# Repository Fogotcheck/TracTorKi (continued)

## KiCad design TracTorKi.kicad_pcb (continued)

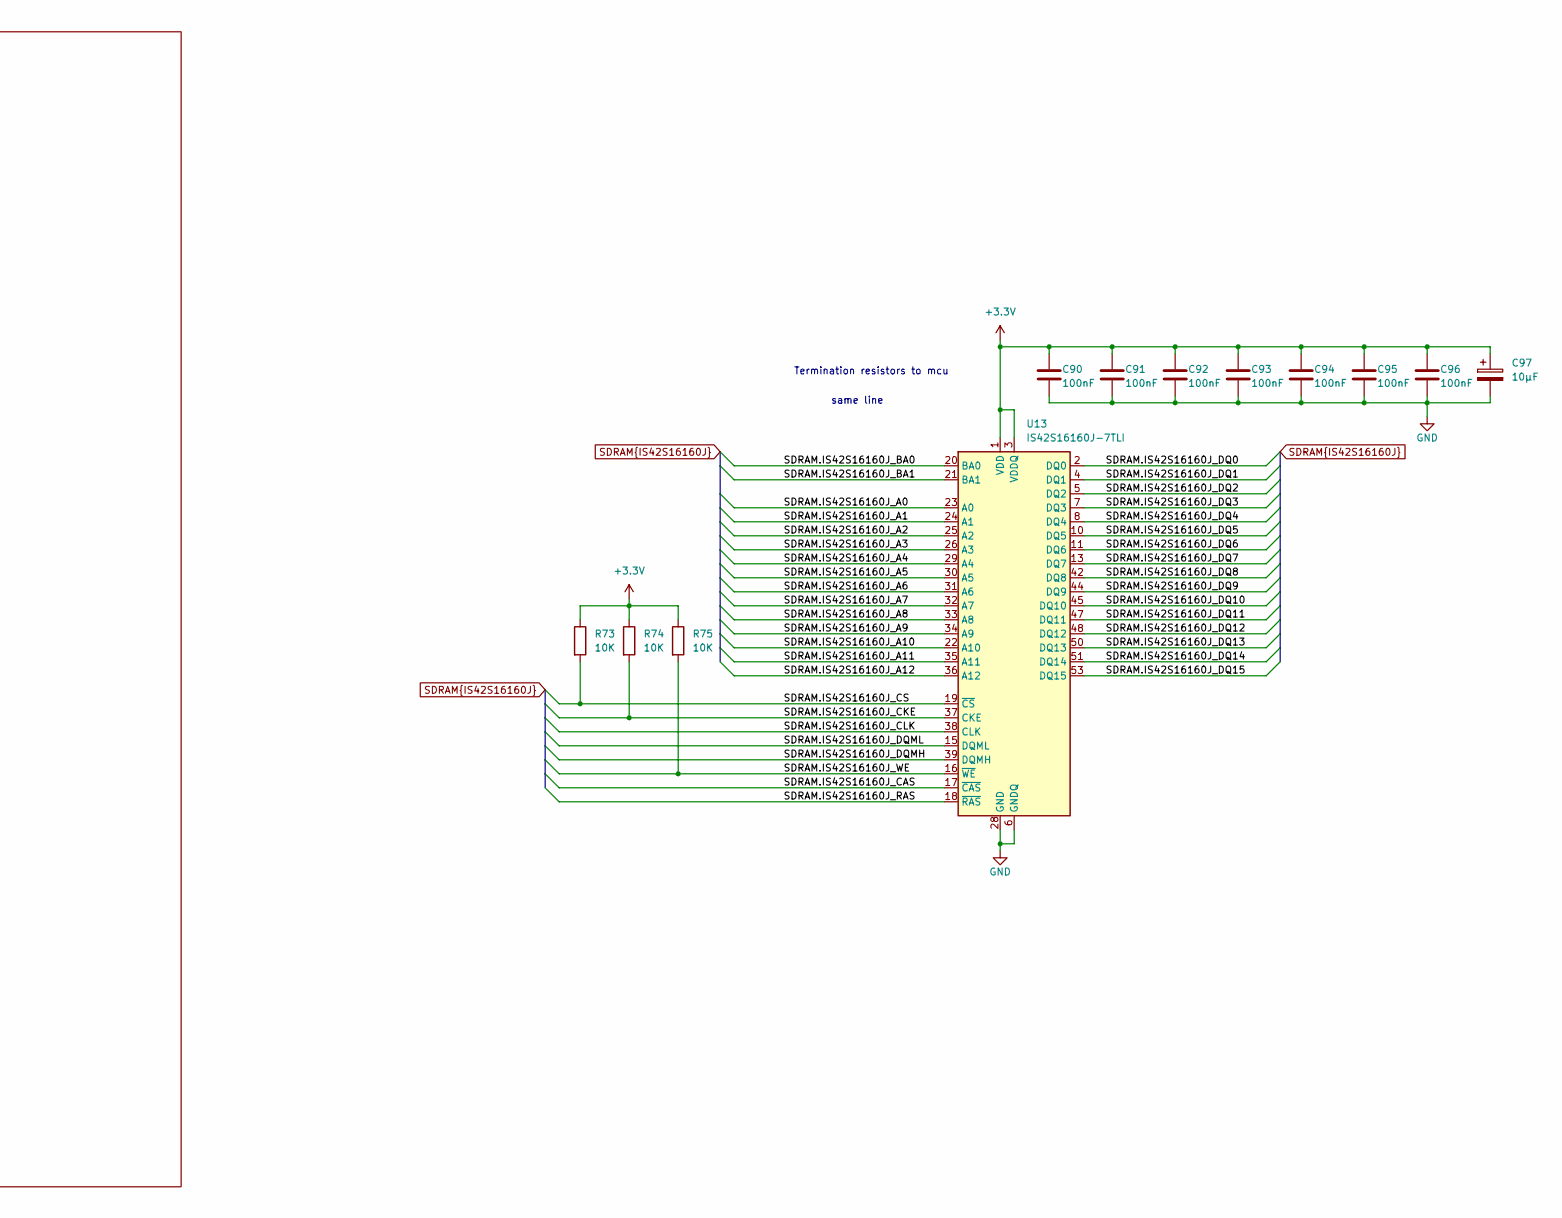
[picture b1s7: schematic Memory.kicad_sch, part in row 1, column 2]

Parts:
C90, C91, C92, C93, C94, C95, C96: 100nF; C_0402_1005Metric_Pad0.74x0.62mm_HandSolder
C97: 10µF; CP_EIA-3216-18_Kemet-A_HandSolder
R73, R74, R75: 10K; R_0603_1608Metric_Pad0.98x0.95mm_HandSolder
U13: IS42S16160J-7TLI; TSOP-II-54_22.2x10.16mm_P0.8mm

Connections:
+3.3V: C90.1, C91.1, C92.1, C93.1, C94.1, C95.1, C96.1, C97.1, R73.1, R74.1, R75.1, U13.1 (VDD), U13.3 (VDDQ), U13.9 (VDDQ), U13.14 (VDD), U13.27 (VDD), U13.43 (VDDQ), U13.49 (VDDQ); also elsewhere on the board
GND: C90.2, C91.2, C92.2, C93.2, C94.2, C95.2, C96.2, C97.2, U13.6 (GNDQ), U13.12 (GNDQ), U13.28 (GND), U13.41 (GND), U13.46 (GNDQ), U13.52 (GNDQ), U13.54 (GND); also elsewhere on the board
SDRAM.IS42S16160J_A0: U13.23 (A0); also elsewhere on the board
SDRAM.IS42S16160J_A1: U13.24 (A1); also elsewhere on the board
SDRAM.IS42S16160J_A2: U13.25 (A2); also elsewhere on the board
SDRAM.IS42S16160J_A3: U13.26 (A3); also elsewhere on the board
SDRAM.IS42S16160J_A4: U13.29 (A4); also elsewhere on the board
SDRAM.IS42S16160J_A5: U13.30 (A5); also elsewhere on the board
SDRAM.IS42S16160J_A6: U13.31 (A6); also elsewhere on the board
SDRAM.IS42S16160J_A7: U13.32 (A7); also elsewhere on the board
SDRAM.IS42S16160J_A8: U13.33 (A8); also elsewhere on the board
SDRAM.IS42S16160J_A9: U13.34 (A9); also elsewhere on the board
SDRAM.IS42S16160J_A10: U13.22 (A10); also elsewhere on the board
SDRAM.IS42S16160J_A11: U13.35 (A11); also elsewhere on the board
SDRAM.IS42S16160J_A12: U13.36 (A12); also elsewhere on the board
SDRAM.IS42S16160J_BA0: U13.20 (BA0); also elsewhere on the board
SDRAM.IS42S16160J_BA1: U13.21 (BA1); also elsewhere on the board
SDRAM.IS42S16160J_CAS: U13.17 (~CAS); also elsewhere on the board
SDRAM.IS42S16160J_CKE: R74.2, U13.37 (CKE); also elsewhere on the board
SDRAM.IS42S16160J_CLK: U13.38 (CLK); also elsewhere on the board
SDRAM.IS42S16160J_CS: R73.2, U13.19 (~CS); also elsewhere on the board
SDRAM.IS42S16160J_DQ0: U13.2 (DQ0); also elsewhere on the board
SDRAM.IS42S16160J_DQ1: U13.4 (DQ1); also elsewhere on the board
SDRAM.IS42S16160J_DQ2: U13.5 (DQ2); also elsewhere on the board
SDRAM.IS42S16160J_DQ3: U13.7 (DQ3); also elsewhere on the board
SDRAM.IS42S16160J_DQ4: U13.8 (DQ4); also elsewhere on the board
SDRAM.IS42S16160J_DQ5: U13.10 (DQ5); also elsewhere on the board
SDRAM.IS42S16160J_DQ6: U13.11 (DQ6); also elsewhere on the board
SDRAM.IS42S16160J_DQ7: U13.13 (DQ7); also elsewhere on the board
SDRAM.IS42S16160J_DQ8: U13.42 (DQ8); also elsewhere on the board
SDRAM.IS42S16160J_DQ9: U13.44 (DQ9); also elsewhere on the board
SDRAM.IS42S16160J_DQ10: U13.45 (DQ10); also elsewhere on the board
SDRAM.IS42S16160J_DQ11: U13.47 (DQ11); also elsewhere on the board
SDRAM.IS42S16160J_DQ12: U13.48 (DQ12); also elsewhere on the board
SDRAM.IS42S16160J_DQ13: U13.50 (DQ13); also elsewhere on the board
SDRAM.IS42S16160J_DQ14: U13.51 (DQ14); also elsewhere on the board
SDRAM.IS42S16160J_DQ15: U13.53 (DQ15); also elsewhere on the board
SDRAM.IS42S16160J_DQMH: U13.39 (DQMH); also elsewhere on the board
SDRAM.IS42S16160J_DQML: U13.15 (DQML); also elsewhere on the board
SDRAM.IS42S16160J_RAS: U13.18 (~RAS); also elsewhere on the board
SDRAM.IS42S16160J_WE: R75.2, U13.16 (~WE); also elsewhere on the board

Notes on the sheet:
Termination resistors to mcu
same line

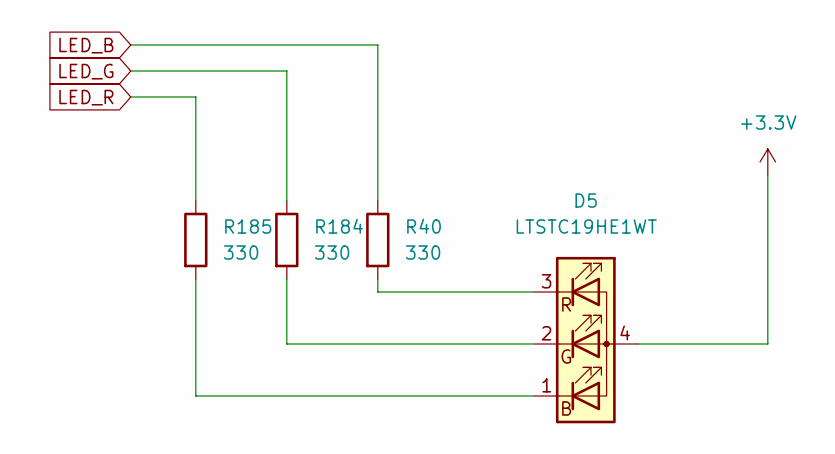
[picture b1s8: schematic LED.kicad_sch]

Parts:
D5: LTSTC19HE1WT; LED_LiteOn_LTST-C19HE1WT
R40, R184, R185: 330; R_0603_1608Metric_Pad0.98x0.95mm_HandSolder

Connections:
+3.3V: D5.4 (A); also elsewhere on the board
LED_B: R40.1; also elsewhere on the board
LED_G: R184.1; also elsewhere on the board
LED_R: R185.1; also elsewhere on the board
unnamed: D5.1 (BK), R185.2
unnamed: D5.2 (GK), R184.2
unnamed: D5.3 (RK), R40.2

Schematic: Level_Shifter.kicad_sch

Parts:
C135, C136: 0.1µF; C_0603_1608Metric_Pad1.08x0.95mm_HandSolder
R38, R41: 20K; R_0603_1608Metric_Pad0.98x0.95mm_HandSolder
R175, R176, R177, R178, R179, R180, R181, R182, R183: 4.7K; R_0603_1608Metric_Pad0.98x0.95mm_HandSolder
U19: TCA9517ADGK; VSSOP-8_3x3mm_P0.65mm

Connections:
+3.3V: C136.1, R175.1, R176.1, R180.1, R181.1, R182.1, R183.1, U19.1 (VCCA); also elsewhere on the board
+5V: C135.1, R177.1, R178.1, R179.1, U19.8 (VCCB); also elsewhere on the board
BQ25798_CE: R41.1; also elsewhere on the board
BQ25798_INT: R183.2; also elsewhere on the board
BQ25798_QON: R181.2; also elsewhere on the board
BQ25798_SCL: R179.2, U19.7 (SCLB); also elsewhere on the board
BQ25798_SDA: R178.2, U19.6 (SDAB); also elsewhere on the board
BQ25798_STAT: R182.2; also elsewhere on the board
GND: C135.2, C136.2, R38.2, R41.2, U19.4 (GND); also elsewhere on the board
unnamed: R177.2, U19.5 (EN)
POWER_I2C_SCL: R175.2, U19.2 (SCLA); also elsewhere on the board
POWER_I2C_SDA: R176.2, U19.3 (SDAA); also elsewhere on the board
STUSB4500_INT: R180.2; also elsewhere on the board
STUSB4500_RST: R38.1; also elsewhere on the board

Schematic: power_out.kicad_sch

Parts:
C37, C38, C44, C45, C46, C47, C52, C53, C54, C55, C63, C64, C65, C66: 22µF; C_0603_1608Metric_Pad1.08x0.95mm_HandSolder
C39, C43, C51, C62: 0.1µF; C_0603_1608Metric_Pad1.08x0.95mm_HandSolder
C40, C48, C57: 10µF; C_1206_3216Metric_Pad1.33x1.80mm_HandSolder; voltage 50V
C41, C50, C61: 1µF; C_0603_1608Metric_Pad1.08x0.95mm_HandSolder
C42, C49, C58: 220nF; C_1206_3216Metric_Pad1.33x1.80mm_HandSolder; voltage 50V
C56: 33µF; CP_EIA-7343-31_Kemet-D_HandSolder; voltage 50V
L2: 8.2µH; L_Chilisin_BMRx00060630
L3: 15µH; L_Chilisin_BMRx00060630
L4: 6.8µH; L_Chilisin_BMRx00060630
R32: 3.57; R_0603_1608Metric_Pad0.98x0.95mm_HandSolder
R33: 1.15; R_0603_1608Metric_Pad0.98x0.95mm_HandSolder
R34, R36, R39: 100K; R_0603_1608Metric_Pad0.98x0.95mm_HandSolder
R35: 24.9K; R_0603_1608Metric_Pad0.98x0.95mm_HandSolder
R37: 9.09K; R_0603_1608Metric_Pad0.98x0.95mm_HandSolder
R42: 38.3K; R_0603_1608Metric_Pad0.98x0.95mm_HandSolder
U4, U5, U6: LMR33630ADDA; Texas_HSOP-8-1EP_3.9x4.9mm_P1.27mm_ThermalVias
U7: TPS7A9201DSKR; Texas_S-PDSO-N10_EP1.2x2mm

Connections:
3.6V: C38.1, C63.1, C64.1, C65.1, C66.1, L4.2, R39.1, U7.7 (EN), U7.9 (IN), U7.10 (IN)
+3.3V: C37.1, R32.2, U7.1 (OUT), U7.2 (OUT); also elsewhere on the board
+5V: C44.1, C45.1, C46.1, C47.1, L2.2, R34.1; also elsewhere on the board
+12V: C52.1, C53.1, C54.1, C55.1, C56.1, L3.2, R36.1; also elsewhere on the board
GND: C37.2, C38.2, C39.2, C40.2, C41.2, C42.2, C44.2, C45.2, C46.2, C47.2, C48.2, C49.2, C50.2, C52.2, C53.2, C54.2, C55.2, C56.2, C57.2, C58.2, C61.2, C63.2, C64.2, C65.2, C66.2, R33.2, R35.2, R37.2, R42.2, U4.1 (GND), U4.9 (GND), U5.1 (GND), U5.9 (GND), U6.1 (GND), U6.9 (GND), U7.4 (GND), U7.6 (SS_CTRL), U7.11 (GND); also elsewhere on the board
unnamed: C43.1, C43.2, L3.1, U4.7 (BOOT), U4.8 (SW)
unnamed: R36.2, R37.1, U4.5 (FB)
unnamed: C50.1, U4.6 (VCC)
unnamed: C51.1, C51.2, L2.1, U5.7 (BOOT), U5.8 (SW)
unnamed: R34.2, R35.1, U5.5 (FB)
unnamed: C41.1, U5.6 (VCC)
unnamed: C62.1, C62.2, L4.1, U6.7 (BOOT), U6.8 (SW)
unnamed: R39.2, R42.1, U6.5 (FB)
unnamed: C61.1, U6.6 (VCC)
unnamed: R32.1, R33.1, U7.3 (FB)
unnamed: C39.1, U7.8 (NR/SS)
SYSTEM_LOAD: C40.1, C42.1, C48.1, C49.1, C57.1, C58.1, U4.2 (VIN), U4.3 (EN), U5.2 (VIN), U5.3 (EN), U6.2 (VIN), U6.3 (EN); also elsewhere on the board

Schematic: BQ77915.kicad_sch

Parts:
C30, C31: 1µF; C_1206_3216Metric_Pad1.33x1.80mm_HandSolder; voltage X7R, 50V
C32, C33, C34, C35, C36: 1µF; C_0603_1608Metric_Pad1.08x0.95mm_HandSolder
C67, C68, C69: 0.1µF; C_0603_1608Metric_Pad1.08x0.95mm_HandSolder
J2: Conn_01x03_Pin; Molex_Micro-Latch_53254-0370_1x03_P2.00mm_Horizontal
J15: Conn_01x05_Pin; Molex_Micro-Fit_3.0_43650-0500_1x05_P3.00mm_Horizontal
Q4, Q5: CSD17577Q3A; VSON-8_3.3x3.3mm_P0.65mm_NexFET
R16: 470; R_1206_3216Metric_Pad1.30x1.75mm_HandSolder
R17, R18, R19, R20, R21, R25: 1K; R_0603_1608Metric_Pad0.98x0.95mm_HandSolder
R22: 1mΩ; R_2512_6332Metric_Pad1.40x3.35mm_HandSolder
R23: 4.5K; R_0603_1608Metric_Pad0.98x0.95mm_HandSolder
R24, R26: 1M; R_0603_1608Metric_Pad0.98x0.95mm_HandSolder
R27: 470K; R_0603_1608Metric_Pad0.98x0.95mm_HandSolder
R28, R30: 10K; R_0603_1608Metric_Pad0.98x0.95mm_HandSolder
R29: 604K; R_0603_1608Metric_Pad0.98x0.95mm_HandSolder
R31: 10K; R_1206_3216Metric_Pad1.30x1.75mm_HandSolder
R43, R44: 100; R_0603_1608Metric_Pad0.98x0.95mm_HandSolder
U3: BQ7791500PWR; TSSOP-24_4.4x7.8mm_P0.65mm

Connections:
BAT_1: J15.4, R20.1
BAT_2: J15.3, R19.1
BAT_3: J15.2, R18.1
BAT_4: J15.1, R16.1, R17.1; also elsewhere on the board
BAT_GND: C35.1, C36.2, C67.1, C67.2, C69.1, J15.5, R21.1, R22.1, R28.2, R29.2, R44.2, U3.9 (VSS), U3.23 (CTRC), U3.24 (CTRD)
BQ25798_NTC: J2.2; also elsewhere on the board
BQ77915_NTC: J2.1, R30.2, U3.18 (TS)
BQ77915_SHUNT: C69.2, Q4.1 (S), Q4.2 (S), Q4.3 (S), R22.2, R24.2, R43.2
BQ77915_SRN: C68.2, R43.1, U3.11 (SRN)
BQ77915_SRP: C68.1, R44.1, U3.10 (SRP)
GND: C30.2, C31.1, J2.3, Q5.1 (S), Q5.2 (S), Q5.3 (S), R26.2, R27.2; also elsewhere on the board
unnamed: Q4.5 (D), Q5.5 (D)
unnamed: Q4.4 (G), R23.2, R24.1
unnamed: Q5.4 (G), R25.2, R26.1
unnamed: C30.1, U3.2 (AVDD), U3.20 (CCFG)
unnamed: R28.1, U3.16 (CBI)
unnamed: R25.1, U3.13 (CHG)
unnamed: R23.1, U3.12 (DSG)
unnamed: R27.1, U3.14 (LD)
unnamed: R29.1, U3.17 (OCDP)
unnamed: R31.2, U3.22 (PRES)
unnamed: C36.1, R21.2, U3.8 (VC0)
unnamed: C34.1, C35.2, R20.2, U3.7 (VC1)
unnamed: C33.1, C34.2, R19.2, U3.6 (VC2)
unnamed: C32.1, C33.2, R18.2, U3.5 (VC3)
unnamed: C32.2, R17.2, U3.3 (VC5), U3.4 (VC4)
unnamed: C31.2, R16.2, R31.1, U3.1 (VDD)
unnamed: R30.1, U3.19 (VTB)

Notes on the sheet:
дифференциальная пара

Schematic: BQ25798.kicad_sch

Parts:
C6: 4.7 µF; C_1206_3216Metric_Pad1.33x1.80mm_HandSolder; voltage X7R, 50V
C7: 47 nF; C_1206_3216Metric_Pad1.33x1.80mm_HandSolder; voltage X7R, 50V
C8, C9, C10, C11, C13, C14, C15, C19, C22, C25, C26, C27: 10µF; C_1206_3216Metric_Pad1.33x1.80mm_HandSolder; voltage X7R, 50V
C12, C21, C23, C24: 0.1µF; C_1206_3216Metric_Pad1.33x1.80mm_HandSolder; voltage X7R, 50V
C16: 1nF; C_1206_3216Metric_Pad1.33x1.80mm_HandSolder; Voltage 50V
C17, C18: 47 nF; C_0603_1608Metric_Pad1.08x0.95mm_HandSolder; voltage X7R, 50V
C20: 2.2µF; C_1206_3216Metric_Pad1.33x1.80mm_HandSolder; voltage X7R, 50V
C28, C29: 33µF; CP_EIA-7343-31_Kemet-D_HandSolder; voltage 50V
L1: 2.2 µH; L_Chilisin_BMRx00060630
Q3: CSD17577Q3A; VSON-8_3.3x3.3mm_P0.65mm_NexFET
R9: 100K; R_0603_1608Metric_Pad0.98x0.95mm_HandSolder
R10: 150K; R_0603_1608Metric_Pad0.98x0.95mm_HandSolder
R11: 27K; R_0603_1608Metric_Pad0.98x0.95mm_HandSolder
R12: 30.31K; R_0603_1608Metric_Pad0.98x0.95mm_HandSolder
R13: 5.24K; R_0603_1608Metric_Pad0.98x0.95mm_HandSolder
R14: 100; R_1206_3216Metric_Pad1.30x1.75mm_HandSolder
R15: 2; R_1206_3216Metric_Pad1.30x1.75mm_HandSolder
U1: BQ25798RQMR; Texas_RQM0029A_VQFN-29_4x4mm_P0.4mm

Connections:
+20V: C19.1, C21.1, C22.1, C23.1, R15.1, U1.2 (VBUS), U1.3 (VBUS), U1.8 (VAC2), U1.9 (VAC1); also elsewhere on the board
BAT_4: Q3.5 (D), R14.1; also elsewhere on the board
BQ25798_CE: U1.13 (~CE); also elsewhere on the board
BQ25798_INT: U1.21 (~INT); also elsewhere on the board
BQ25798_NTC: R12.1, R13.2, U1.16 (TS); also elsewhere on the board
BQ25798_QON: U1.12 (~QON); also elsewhere on the board
BQ25798_SCL: U1.14 (SCL); also elsewhere on the board
BQ25798_SDA: U1.15 (SDA); also elsewhere on the board
BQ25798_STAT: U1.1 (STAT); also elsewhere on the board
GND: C6.2, C7.2, C8.2, C9.2, C10.2, C11.2, C12.2, C13.2, C14.2, C15.2, C16.2, C19.2, C20.2, C21.2, C22.2, C23.2, C24.2, C25.2, C26.2, C27.2, C28.2, C29.2, R10.2, R11.2, R12.2, U1.10 (ACDRV2), U1.11 (ACDRV1), U1.27 (GND); also elsewhere on the board
unnamed: C8.1, C9.1, Q3.1 (S), Q3.2 (S), Q3.3 (S), U1.22 (BAT), U1.23 (BAT)
unnamed: C20.1, R15.2
unnamed: C16.1, Q3.4 (G), U1.24 (SDRV)
unnamed: C7.1, R14.2, U1.18 (BATP)
unnamed: C18.1, U1.4 (BTST1)
unnamed: C17.2, U1.19 (BTST2)
unnamed: R9.1, R10.1, U1.17 (ILIM_HIZ)
unnamed: C24.1, C25.1, C26.1, C27.1, C28.1, C29.1, U1.29 (PMID)
unnamed: R11.1, U1.20 (PROG)
unnamed: C18.2, L1.1, U1.28 (SW1)
unnamed: C17.1, L1.2, U1.26 (SW2)
REGN: C6.1, R9.2, R13.1, U1.5 (REGN)
SYSTEM_LOAD: C10.1, C11.1, C12.1, C13.1, C14.1, C15.1, U1.25 (SYS); also elsewhere on the board
USB_DM: U1.7 (D-); also elsewhere on the board
USB_DP: U1.6 (D+); also elsewhere on the board

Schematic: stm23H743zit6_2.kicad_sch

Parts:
C107, C108: 2.2uF; C_0603_1608Metric_Pad1.08x0.95mm_HandSolder
C109, C110: 1uF; C_0603_1608Metric_Pad1.08x0.95mm_HandSolder
C111, C112, C114, C115, C117, C118, C120, C121, C123, C124, C125, C126, C128: 100nF; C_0402_1005Metric_Pad0.74x0.62mm_HandSolder
C113, C116, C119, C122: 4.7uF; CP_EIA-3216-18_Kemet-A_HandSolder
C129: 1uF; CP_EIA-2012-12_Kemet-R_HandSolder
FB2: FBMJ1608HM180NTR; L_0603_1608Metric_Pad1.05x0.95mm_HandSolder
U18: STM32H743ZIT6; LQFP144-20x20mm; Manufacturer_Part_Number STM32H743ZIT6

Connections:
+3.3V: C109.1, C110.1, C111.1, C112.1, C113.1, C114.1, C115.1, C116.1, C117.1, C118.1, C119.1, C120.1, C121.1, C122.1, C123.1, C124.1, C125.1, FB2.1, U18.6 (VBAT), U18.17 (VDD), U18.30 (VDD), U18.39 (VDD), U18.52 (VDD), U18.62 (VDD), U18.72 (VDD), U18.84 (VDD), U18.95 (VDD33USB), U18.108 (VDD), U18.121 (VDD), U18.131 (VDD), U18.144 (VDD); also elsewhere on the board
GND: C107.2, C108.2, C109.2, C110.2, C111.2, C112.2, C113.2, C114.2, C115.2, C116.2, C117.2, C118.2, C119.2, C120.2, C121.2, C122.2, C123.2, C124.2, C125.2, C126.2, C128.2, C129.2, U18.16 (VSS), U18.31 (VSSA), U18.38 (VSS), U18.51 (VSS), U18.61 (VSS), U18.83 (VSS), U18.94 (VSS), U18.107 (VSS), U18.120 (VSS), U18.130 (VSS); also elsewhere on the board
unnamed: C108.1, U18.71 (VCAP1)
unnamed: C107.1, U18.106 (VCAP2)
VDDA: C126.1, C128.1, C129.1, FB2.2, U18.32 (VREF+), U18.33 (VDDA)

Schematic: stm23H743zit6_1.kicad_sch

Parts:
C130, C131: 6.8pF; C_0603_1608Metric_Pad1.08x0.95mm_HandSolder
C132: 100nF; C_0603_1608Metric_Pad1.08x0.95mm_HandSolder
D4: ESDALC6V1-W2; SOT-323_SC-70
R129, R131: 10K; R_0603_1608Metric_Pad0.98x0.95mm_HandSolder
R130: 10K; R_0805_2012Metric_Pad1.20x1.40mm_HandSolder
R132, R133, R134, R135, R136, R137, R138, R139, R140, R141, R142, R143, R144, R145, R146, R147, R148, R149, R150, R151, R152, R153, R154, R155, R156, R157, R158, R159, R160: 33; R_0402_1005Metric_Pad0.72x0.64mm_HandSolder
SW1: CK_KMS2xxG; SW_SPST_CK_KMS2xxGP
U18: STM32H743ZIT6; LQFP144-20x20mm; Manufacturer_Part_Number STM32H743ZIT6
Y2: NX3225HA-25MHz-EXS00A-CH00343; Crystal_SMD_3225-4Pin_3.2x2.5mm_HandSoldering

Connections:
+3.3V: R129.1, R131.1; also elsewhere on the board
BNO085_INT: U18.3 (PE4); also elsewhere on the board
BQ25798_INT: U18.4 (PE5); also elsewhere on the board
BQ25798_QON: U18.91 (PG6); also elsewhere on the board
BTS7960_IS_L1_TO_MCU: U18.19 (PF7); also elsewhere on the board
BTS7960_IS_L2_TO_MCU: U18.20 (PF8); also elsewhere on the board
BTS7960_IS_R1_TO_MCU: U18.21 (PF9); also elsewhere on the board
BTS7960_IS_R2_TO_MCU: U18.22 (PF10); also elsewhere on the board
GND: C130.2, C131.2, C132.2, D4.1 (A), R130.2, SW1.2, SW1.SH (B), Y2.2 (G), Y2.4 (G); also elsewhere on the board
LED_G: U18.129 (PG14); also elsewhere on the board
MCU_BOOT0: R130.1, U18.138 (BOOT0)
MCU_RESET: C132.1, D4.3 (K), R131.2, SW1.1, U18.25 (NRST); also elsewhere on the board
unnamed: R129.2, U18.143 (PDR_ON)
unnamed: R133.2, U18.141 (PE0)
unnamed: R132.2, U18.142 (PE1)
unnamed: R134.2, U18.58 (PE7)
unnamed: R135.2, U18.59 (PE8)
unnamed: R136.2, U18.60 (PE9)
unnamed: R137.2, U18.63 (PE10)
unnamed: R138.2, U18.64 (PE11)
unnamed: R139.2, U18.65 (PE12)
unnamed: R140.2, U18.66 (PE13)
unnamed: R141.2, U18.67 (PE14)
unnamed: R142.2, U18.68 (PE15)
unnamed: R143.2, U18.10 (PF0)
unnamed: R144.2, U18.11 (PF1)
unnamed: R145.2, U18.12 (PF2)
unnamed: R146.2, U18.13 (PF3)
unnamed: R147.2, U18.14 (PF4)
unnamed: R148.2, U18.15 (PF5)
unnamed: R149.2, U18.49 (PF11)
unnamed: R150.2, U18.50 (PF12)
unnamed: R151.2, U18.53 (PF13)
unnamed: R152.2, U18.54 (PF14)
unnamed: R153.2, U18.55 (PF15)
unnamed: R160.1, U18.56 (PG0)
unnamed: R159.1, U18.57 (PG1)
unnamed: R158.1, U18.87 (PG2)
unnamed: R157.1, U18.89 (PG4)
unnamed: R156.1, U18.90 (PG5)
unnamed: R155.1, U18.93 (PG8)
unnamed: R154.1, U18.132 (PG15)
unnamed: C131.1, U18.23 (PH0-OSC_IN), Y2.3
unnamed: C130.1, U18.24 (PH1-OSC_OUT), Y2.1
SDRAM.IS42S16160J_A0: R143.1; also elsewhere on the board
SDRAM.IS42S16160J_A1: R144.1; also elsewhere on the board
SDRAM.IS42S16160J_A2: R145.1; also elsewhere on the board
SDRAM.IS42S16160J_A3: R146.1; also elsewhere on the board
SDRAM.IS42S16160J_A4: R147.1; also elsewhere on the board
SDRAM.IS42S16160J_A5: R148.1; also elsewhere on the board
SDRAM.IS42S16160J_A6: R150.1; also elsewhere on the board
SDRAM.IS42S16160J_A7: R151.1; also elsewhere on the board
SDRAM.IS42S16160J_A8: R152.1; also elsewhere on the board
SDRAM.IS42S16160J_A9: R153.1; also elsewhere on the board
SDRAM.IS42S16160J_A10: R160.2; also elsewhere on the board
SDRAM.IS42S16160J_A11: R159.2; also elsewhere on the board
SDRAM.IS42S16160J_A12: R158.2; also elsewhere on the board
SDRAM.IS42S16160J_BA0: R157.2; also elsewhere on the board
SDRAM.IS42S16160J_BA1: R156.2; also elsewhere on the board
SDRAM.IS42S16160J_CAS: R154.2; also elsewhere on the board
SDRAM.IS42S16160J_CLK: R155.2; also elsewhere on the board
SDRAM.IS42S16160J_DQ4: R134.1; also elsewhere on the board
SDRAM.IS42S16160J_DQ5: R135.1; also elsewhere on the board
SDRAM.IS42S16160J_DQ6: R136.1; also elsewhere on the board
SDRAM.IS42S16160J_DQ7: R137.1; also elsewhere on the board
SDRAM.IS42S16160J_DQ8: R138.1; also elsewhere on the board
SDRAM.IS42S16160J_DQ9: R139.1; also elsewhere on the board
SDRAM.IS42S16160J_DQ10: R140.1; also elsewhere on the board
SDRAM.IS42S16160J_DQ11: R141.1; also elsewhere on the board
SDRAM.IS42S16160J_DQ12: R142.1; also elsewhere on the board
SDRAM.IS42S16160J_DQMH: R132.1; also elsewhere on the board
SDRAM.IS42S16160J_DQML: R133.1; also elsewhere on the board
SDRAM.IS42S16160J_RAS: R149.1; also elsewhere on the board
VL53LOx_INT_3: U18.1 (PE2); also elsewhere on the board
VL53LOx_INT_4: U18.2 (PE3); also elsewhere on the board
VL53LOx_XSHUT_1: U18.125 (PG10); also elsewhere on the board
VL53LOx_XSHUT_2: U18.126 (PG11); also elsewhere on the board
VL53LOx_XSHUT_3: U18.127 (PG12); also elsewhere on the board
VL53LOx_XSHUT_4: U18.128 (PG13); also elsewhere on the board

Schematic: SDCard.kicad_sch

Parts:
C99: 100nF; C_0402_1005Metric_Pad0.74x0.62mm_HandSolder
C100: 10µF; CP_EIA-3216-18_Kemet-A_HandSolder
J5: Micro_SD_Card_Det1; microSD_HC_Hirose_DM3AT-SF-PEJM5
R77, R78, R79, R80, R81: 10K; R_0603_1608Metric_Pad0.98x0.95mm_HandSolder
U8: IP4252CZ12; Nexperia_HUSON-12_USON-12-1EP_1.35x2.5mm_P0.4mm_EP0.4x2mm

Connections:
+3.3V: C99.1, C100.1, J5.4 (VDD), R77.1, R78.1, R79.1, R80.1, R81.1; also elsewhere on the board
GND: C99.2, C100.2, J5.6 (VSS), J5.10 (SHIELD), U8.13 (GND); also elsewhere on the board
SDCARD.CLK: U8.4 (CH4); also elsewhere on the board
SDCARD.CMD: R78.2, U8.3 (CH3); also elsewhere on the board
SDCARD.D0: R79.2, U8.5 (CH5); also elsewhere on the board
SDCARD.D1: R80.2, U8.6 (CH6); also elsewhere on the board
SDCARD.D2: R81.2, U8.1 (CH1); also elsewhere on the board
SDCARD.D3: R77.2, U8.2 (CH2); also elsewhere on the board
SDCARD._CLK: J5.5 (CLK), U8.9 (CH4)
SDCARD._CMD: J5.3 (CMD), U8.10 (CH3)
SDCARD._DAT0: J5.7 (DAT0), U8.8 (CH5)
SDCARD._DAT1: J5.8 (DAT1), U8.7 (CH6)
SDCARD._DAT2: J5.1 (DAT2), U8.12 (CH1)
SDCARD._DAT3: J5.2 (DAT3/CD), U8.11 (CH2)

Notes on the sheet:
same line

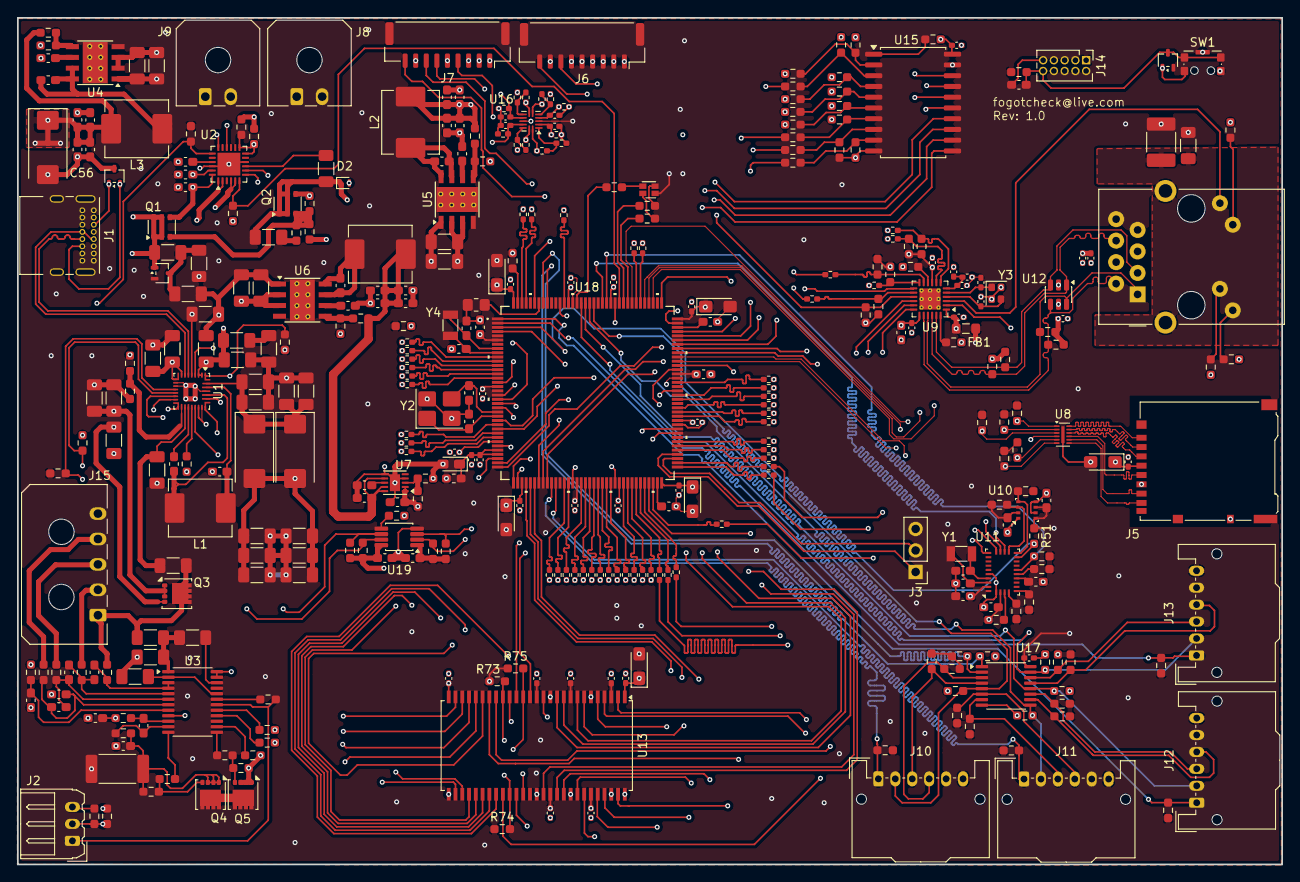
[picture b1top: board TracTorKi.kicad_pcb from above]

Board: 6 copper layers, 149.4 x 100.0 mm, 370 parts (0 on the bottom side), 295 nets.

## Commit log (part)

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2026-03-03 feat: add charger
2026-03-03 feat: add gitignore
2026-03-05 fix: rm TXS0108EPW №1
    - change ACCB -> 5В LM
2026-03-05 fix: change git ignore
2026-03-06 fix: charger schem
2026-03-06 fix: charger
    -rm status OK2,OK3,attach;
2026-03-06 feat: STUSB4500 - add print
2026-03-06 feat: BQ25798, BQ77915 add print
2026-03-06 fix: charger
    - BQ77915 RSNS 1M ->1 mΩ
2026-03-06 fix: BQ77915 charger
    - srnp,snrn - diff pair
2026-03-06 fix: charger style
2026-03-07 feat: add bno085
2026-03-10 fix: refactor, optimize gitignore and remove cache
2026-03-10 fix: refactor move *.kicad_sch -> ./sch
2026-03-10 feat: add readme.md
2026-03-10 fix: refactor move schem
2026-03-10 feat: add ethernet
2026-03-10 fix: ethernet
    Y3 add gnd
2026-03-11 feat: add SDRAM IS42S16160J-7TLI-TR
2026-03-11 feat: add sd card
2026-03-12 feat: add BTS7960
2026-03-12 feat: add VL53LOx
2026-03-12 feat: add stm32h743zit6
2026-03-12 fix: move stm32h743zit6.kicad_sym
2026-03-12 fix: rm legacy lib
2026-03-13 feat: mcu add clock
    - add swd
2026-03-13 feat: memory connect to mcu
2026-03-13 feat; eth connect to mcu
2026-03-13 feat: NC changes
2026-03-13 fix: change gird
2026-03-13 fix: NC changes
2026-03-16 fix: change charger level-shift
    TX0108EPW -> TCA9517ADGK
2026-03-16 fix: change charger connectors
2026-03-16 feat: charger add connect to mcu
2026-03-16 feat: imu add connect to mcu
2026-03-16 feat: motor add connect to mcu
2026-03-16 feat: tof add connect to mcu
2026-03-16 feat: add leds
2026-03-16 fix: swd swap pin
2026-03-16 feat: add usart debug
2026-03-18 feat: trace IS42S16160J-7TLI
2026-03-19 fix: rm trace IS42S16160J
    - add SDRAM_NET
2026-03-19 fix: trace IS42S16160J
2026-03-20 feat: add sdcard trace
    - change rule 3.3V
2026-03-20 fix: resize edge.cuts
    - 100X200
2026-03-20 fix: ethernet align
2026-03-20 fix: rm gnds conn
2026-03-20 feat: add status trace
2026-03-21 feat: trace charger
2026-03-24 fix: move elements
    - retrace ethernet;
    - retrace sdcard;
2026-03-24 feat: trace motor
2026-03-24 feat: trace tof
2026-03-24 feat: trace imu
2026-03-25 fix: fill, 3.3, gnd
2026-03-26 feat: kicad version 9.x.x -> 10.0.0
2026-03-26 fix: pcb style
2026-03-26 fix: rm via vcap
